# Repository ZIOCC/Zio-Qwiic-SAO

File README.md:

# Zio-Qwiic-SAO
Qwiic to SAO badge adapter for Hackaday Supercon 2018

Just a fun little blinky adapter to connect Qwiic modules to the miriad conference badges that feature the SAO connector.

Also a good way to add pullups to the I2C bus of any badge that doesn't already have them.

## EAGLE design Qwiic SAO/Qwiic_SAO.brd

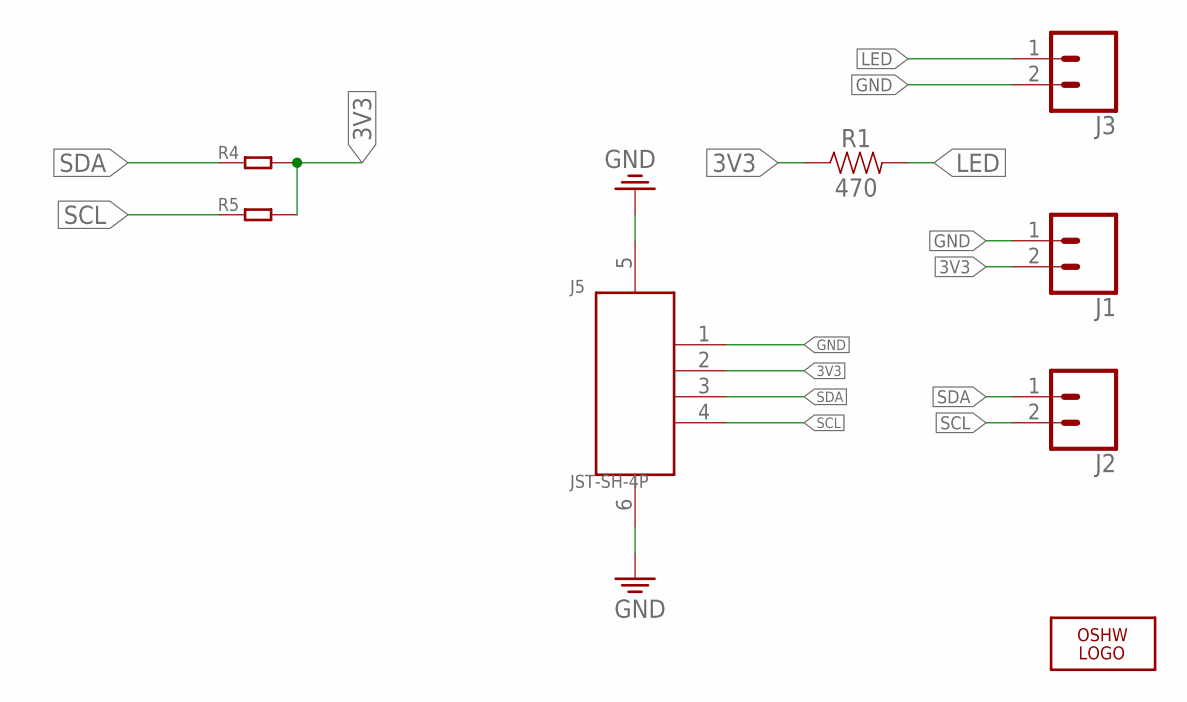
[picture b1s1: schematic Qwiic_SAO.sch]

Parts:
J1, J2, J3: CONN_02; 1X02
J5: JST-SH-4P; SM04B-SRSS-TB
LOGO1: LOGO-OSHW-6MILX0070-NT; OSHW_6X70_NOTEXT
R1: 470; 0603
R4, R5: R-0603; R0603

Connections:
3V3: J1.2, J5.2, R1.1, R4.2, R5.2
GND: J1.1, J3.2, J5.1, J5.5, J5.6
LED: J3.1, R1.2
SCL: J2.2, J5.4, R5.1
SDA: J2.1, J5.3, R4.1

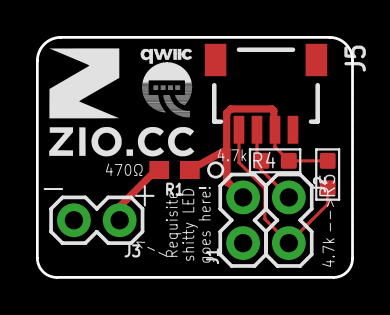
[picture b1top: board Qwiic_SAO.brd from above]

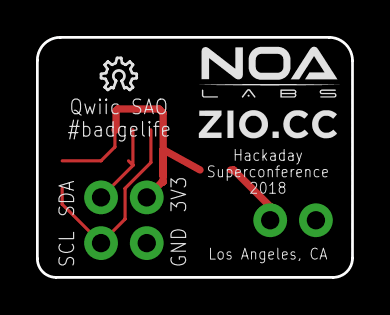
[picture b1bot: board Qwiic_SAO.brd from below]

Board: 2 copper layers, 17.5 x 13.3 mm, 11 parts (2 on the bottom side), 5 nets.

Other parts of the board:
U$1: 6MM
U$2: 1.5MM
U$3: QWIIC-LOGO-SMALL

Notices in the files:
parts and their libraries:
SparkFun-Connectors: Licensing: Creative Commons ShareAlike 4.0 International - https://creativecommons.org/licenses/by-sa/4.0
